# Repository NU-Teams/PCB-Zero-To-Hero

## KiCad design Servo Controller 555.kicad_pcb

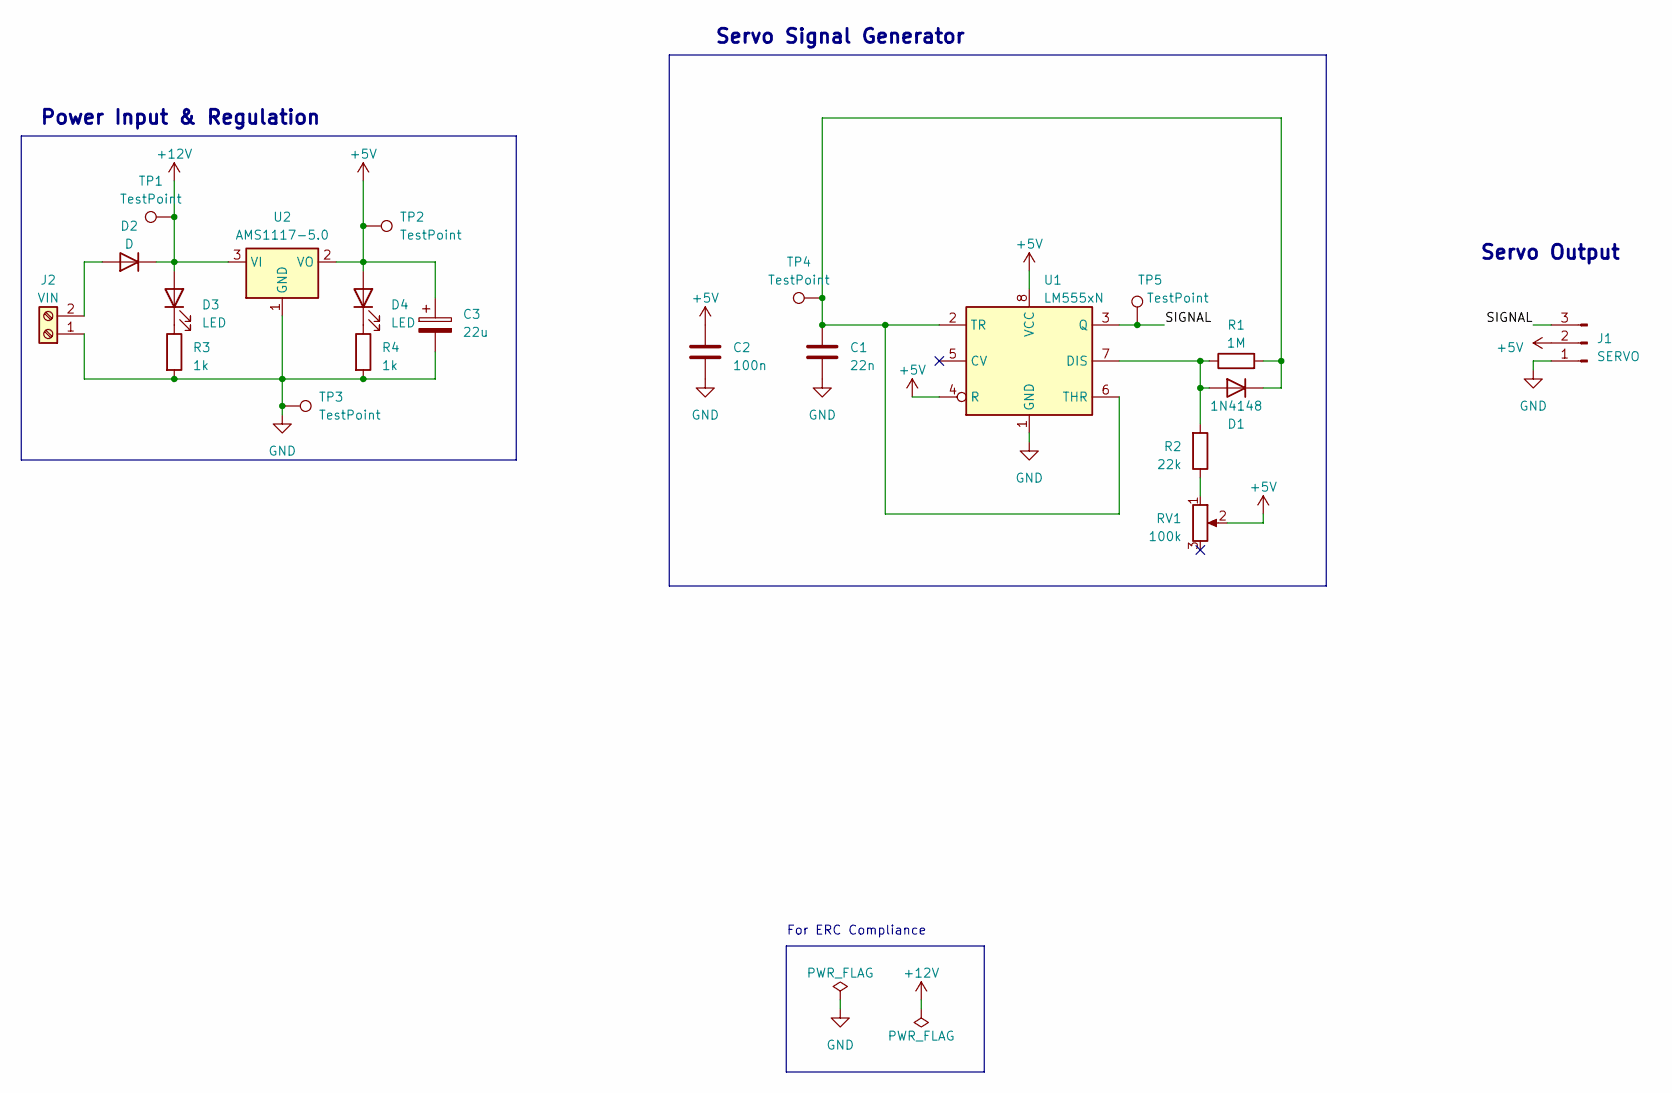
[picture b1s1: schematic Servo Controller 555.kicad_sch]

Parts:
C1: 22n; C_Disc_D3.8mm_W2.6mm_P2.50mm
C2: 100n; C_Disc_D3.8mm_W2.6mm_P2.50mm
C3: 22u; C_0805_2012Metric_Pad1.18x1.45mm_HandSolder
D1: 1N4148; D_DO-35_SOD27_P7.62mm_Horizontal
D2: D; D_SMA_Handsoldering
D3: LED; LED_0805_2012Metric_Pad1.15x1.40mm_HandSolder
D4: LED; LED_D5.0mm
J1: SERVO; PinHeader_1x03_P2.54mm_Vertical
J2: VIN; TerminalBlock_Phoenix_MKDS-1,5-2_1x02_P5.00mm_Horizontal
R1: 1M; R_Axial_DIN0204_L3.6mm_D1.6mm_P7.62mm_Horizontal
R2: 22k; R_Axial_DIN0204_L3.6mm_D1.6mm_P7.62mm_Horizontal
R3: 1k; R_1206_3216Metric
R4: 1k; R_Axial_DIN0204_L3.6mm_D1.6mm_P7.62mm_Horizontal
RV1: 100k; Potentiometer_Bourns_PTV09A-1_Single_Vertical
TP1, TP2, TP3, TP4, TP5: TestPoint; TestPoint_Loop_D1.80mm_Drill1.0mm_Beaded
U1: LM555xN; DIP-8_W7.62mm
U2: AMS1117-5.0; SOT-223-3_TabPin2

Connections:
+5V: C2.1, C3.1, D4.2 (A), J1.2, RV1.2, TP2.1, U1.4 (R), U1.8 (VCC), U2.2 (VO)
+12V: D2.1 (K), D3.2 (A), TP1.1, U2.3 (VI)
/SIGNAL: J1.3, TP5.1, U1.3 (Q)
GND: C1.2, C2.2, C3.2, J1.1, J2.1, R3.2, R4.2, TP3.1, U1.1 (GND), U2.1 (GND)
unnamed: D1.2 (A), R1.1, R2.2, U1.7 (DIS)
unnamed: C1.1, D1.1 (K), R1.2, TP4.1, U1.2 (TR), U1.6 (THR)
unnamed: D2.2 (A), J2.2
unnamed: D3.1 (K), R3.1
unnamed: D4.1 (K), R4.1
unnamed: R2.1, RV1.1

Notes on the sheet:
For ERC Compliance
Servo Output
Power Input & Regulation
Servo Signal Generator

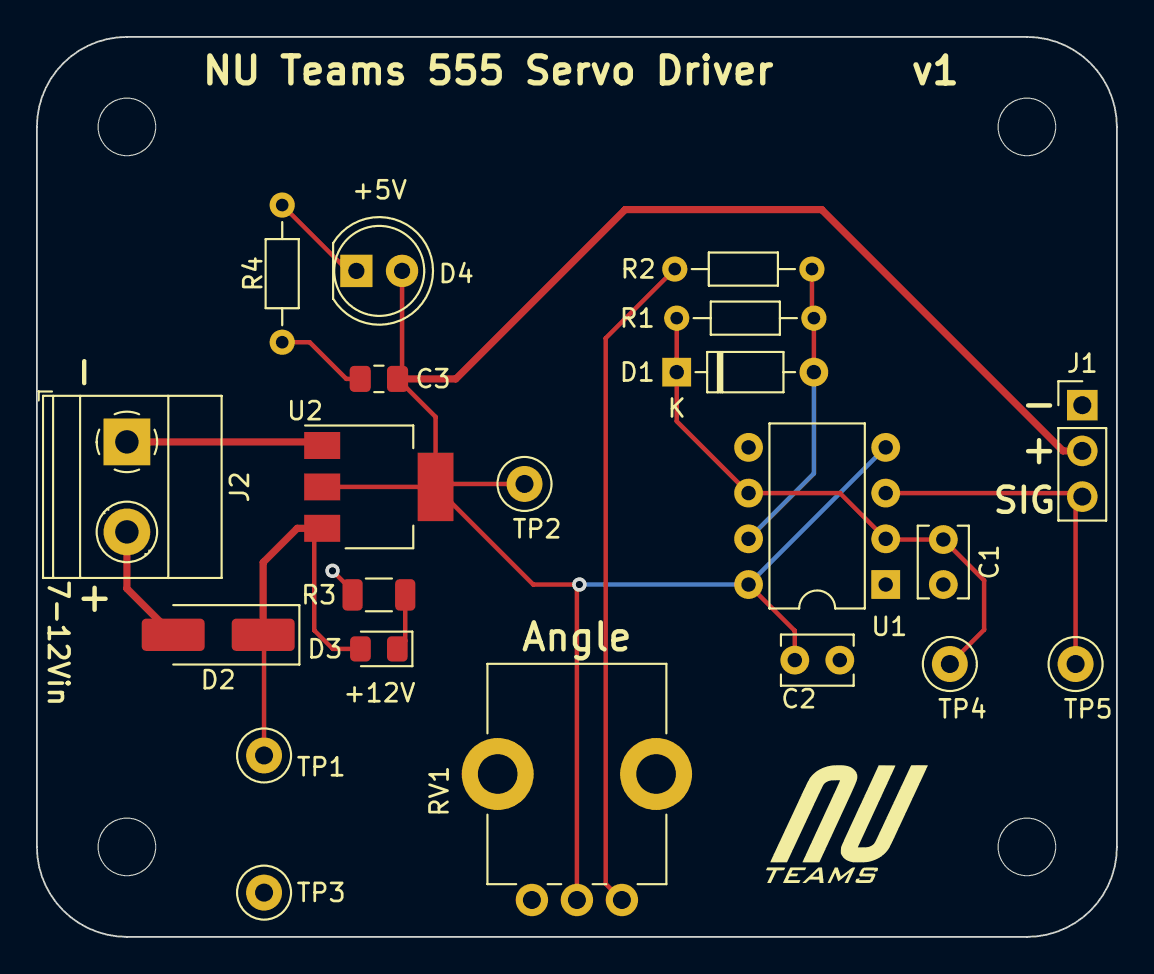
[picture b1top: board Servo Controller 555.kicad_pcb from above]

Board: 2 copper layers, 60.0 x 50.0 mm, 21 parts (0 on the bottom side), 10 nets.

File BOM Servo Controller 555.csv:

#,Reference,Qty,Value,Footprint,Link
1,C1,1,22n,Capacitor_THT:C_Disc_D3.8mm_W2.6mm_P2.50mm,https://www.lcsc.com/product-detail/Ceramic-Disc-Capacitors_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
2,C2,1,100n,Capacitor_THT:C_Disc_D3.8mm_W2.6mm_P2.50mm,https://www.lcsc.com/product-detail/Ceramic-Disc-Capacitors_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
3,C3,1,22u,Capacitor_SMD:C_0805_2012Metric_Pad1.18x1.45mm_HandSolder,https://www.lcsc.com/product-detail/Multilayer-Ceramic-Capac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
4,D1,1,1N4148,Diode_THT:D_DO-35_SOD27_P7.62mm_Horizontal,https://www.lcsc.com/product-detail/Switching-Diode_LGE-1N41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
5,D2,1,D,Diode_SMD:D_SMA_Handsoldering,https://www.lcsc.com/product-detail/Schottky-Barrier-Diodes-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
6,D3,1,LED,LED_SMD:LED_0805_2012Metric_Pad1.15x1.40mm_HandSolder,https://www.lcsc.com/product-detail/Light-Emitting-Diodes-sp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
7,D4,1,LED,LED_THT:LED_D5.0mm,https://www.lcsc.com/product-detail/Light-Emitting-Diodes-sp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
8,J1,1,SERVO,Connector_PinHeader_2.54mm:PinHeader_1x03_P2.54mm_Vertical,https://www.lcsc.com/product-detail/span-style-background-co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
9,J2,1,VIN,"TerminalBlock_Phoenix:TerminalBlock_Phoenix_MKDS-1,5-2_1x02_P5.00mm_Horizontal",https://www.lcsc.com/product-detail/Screw-span-style-backgro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
10,R1,1,1M,Resistor_THT:R_Axial_DIN0204_L3.6mm_D1.6mm_P7.62mm_Horizontal,https://www.lcsc.com/product-detail/Through-Hole-Resistors_V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
11,R2,1,22k,Resistor_THT:R_Axial_DIN0204_L3.6mm_D1.6mm_P7.62mm_Horizontal,https://www.lcsc.com/product-detail/Through-Hole-Resistors_V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
12,R3,1,1k,Resistor_SMD:R_1206_3216Metric,https://www.lcsc.com/product-detail/Chip-span-style-backgrou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
13,R4,1,1k,Resistor_THT:R_Axial_DIN0204_L3.6mm_D1.6mm_P7.62mm_Horizontal,https://www.lcsc.com/product-detail/Through-Hole-Resistors_H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
14,RV1,1,100k,Potentiometer_THT:Potentiometer_Bourns_PTV09A-1_Single_Vertical,https://www.digikey.com.au/en/products/detail/bourns-inc/PTV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
15,"TP1, TP2, TP3, TP4, TP5",5,TestPoint,TestPoint:TestPoint_Loop_D1.80mm_Drill1.0mm_Beaded,https://www.lcsc.com/product-detail/Thimble-Copper-Rod-span-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
16,U1,1,LM555xN,Package_DIP:DIP-8_W7.62mm,https://www.lcsc.com/product-detail/Timers-Clock-Oscillators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
17,U2,1,AMS1117-5.0,Package_TO_SOT_SMD:SOT-223-3_TabPin2,https://www.lcsc.com/product-detail/Linear-Voltage-Regulator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

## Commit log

2023-07-13 Adds as-finished board
